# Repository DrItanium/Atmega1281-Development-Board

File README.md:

This is a simple development board for the QFP version of the ATMEGA1281. The
layout of the connector is an extended superset of the digital header found on
the Arduino Mega + an internal MajorCore development board I have also
created. 

The rest of the pins are laid out to make it trivial to design plugin boards
for my ecore and SxChipset projects.

The board is designed for the AISLER PCB manufacturing service.

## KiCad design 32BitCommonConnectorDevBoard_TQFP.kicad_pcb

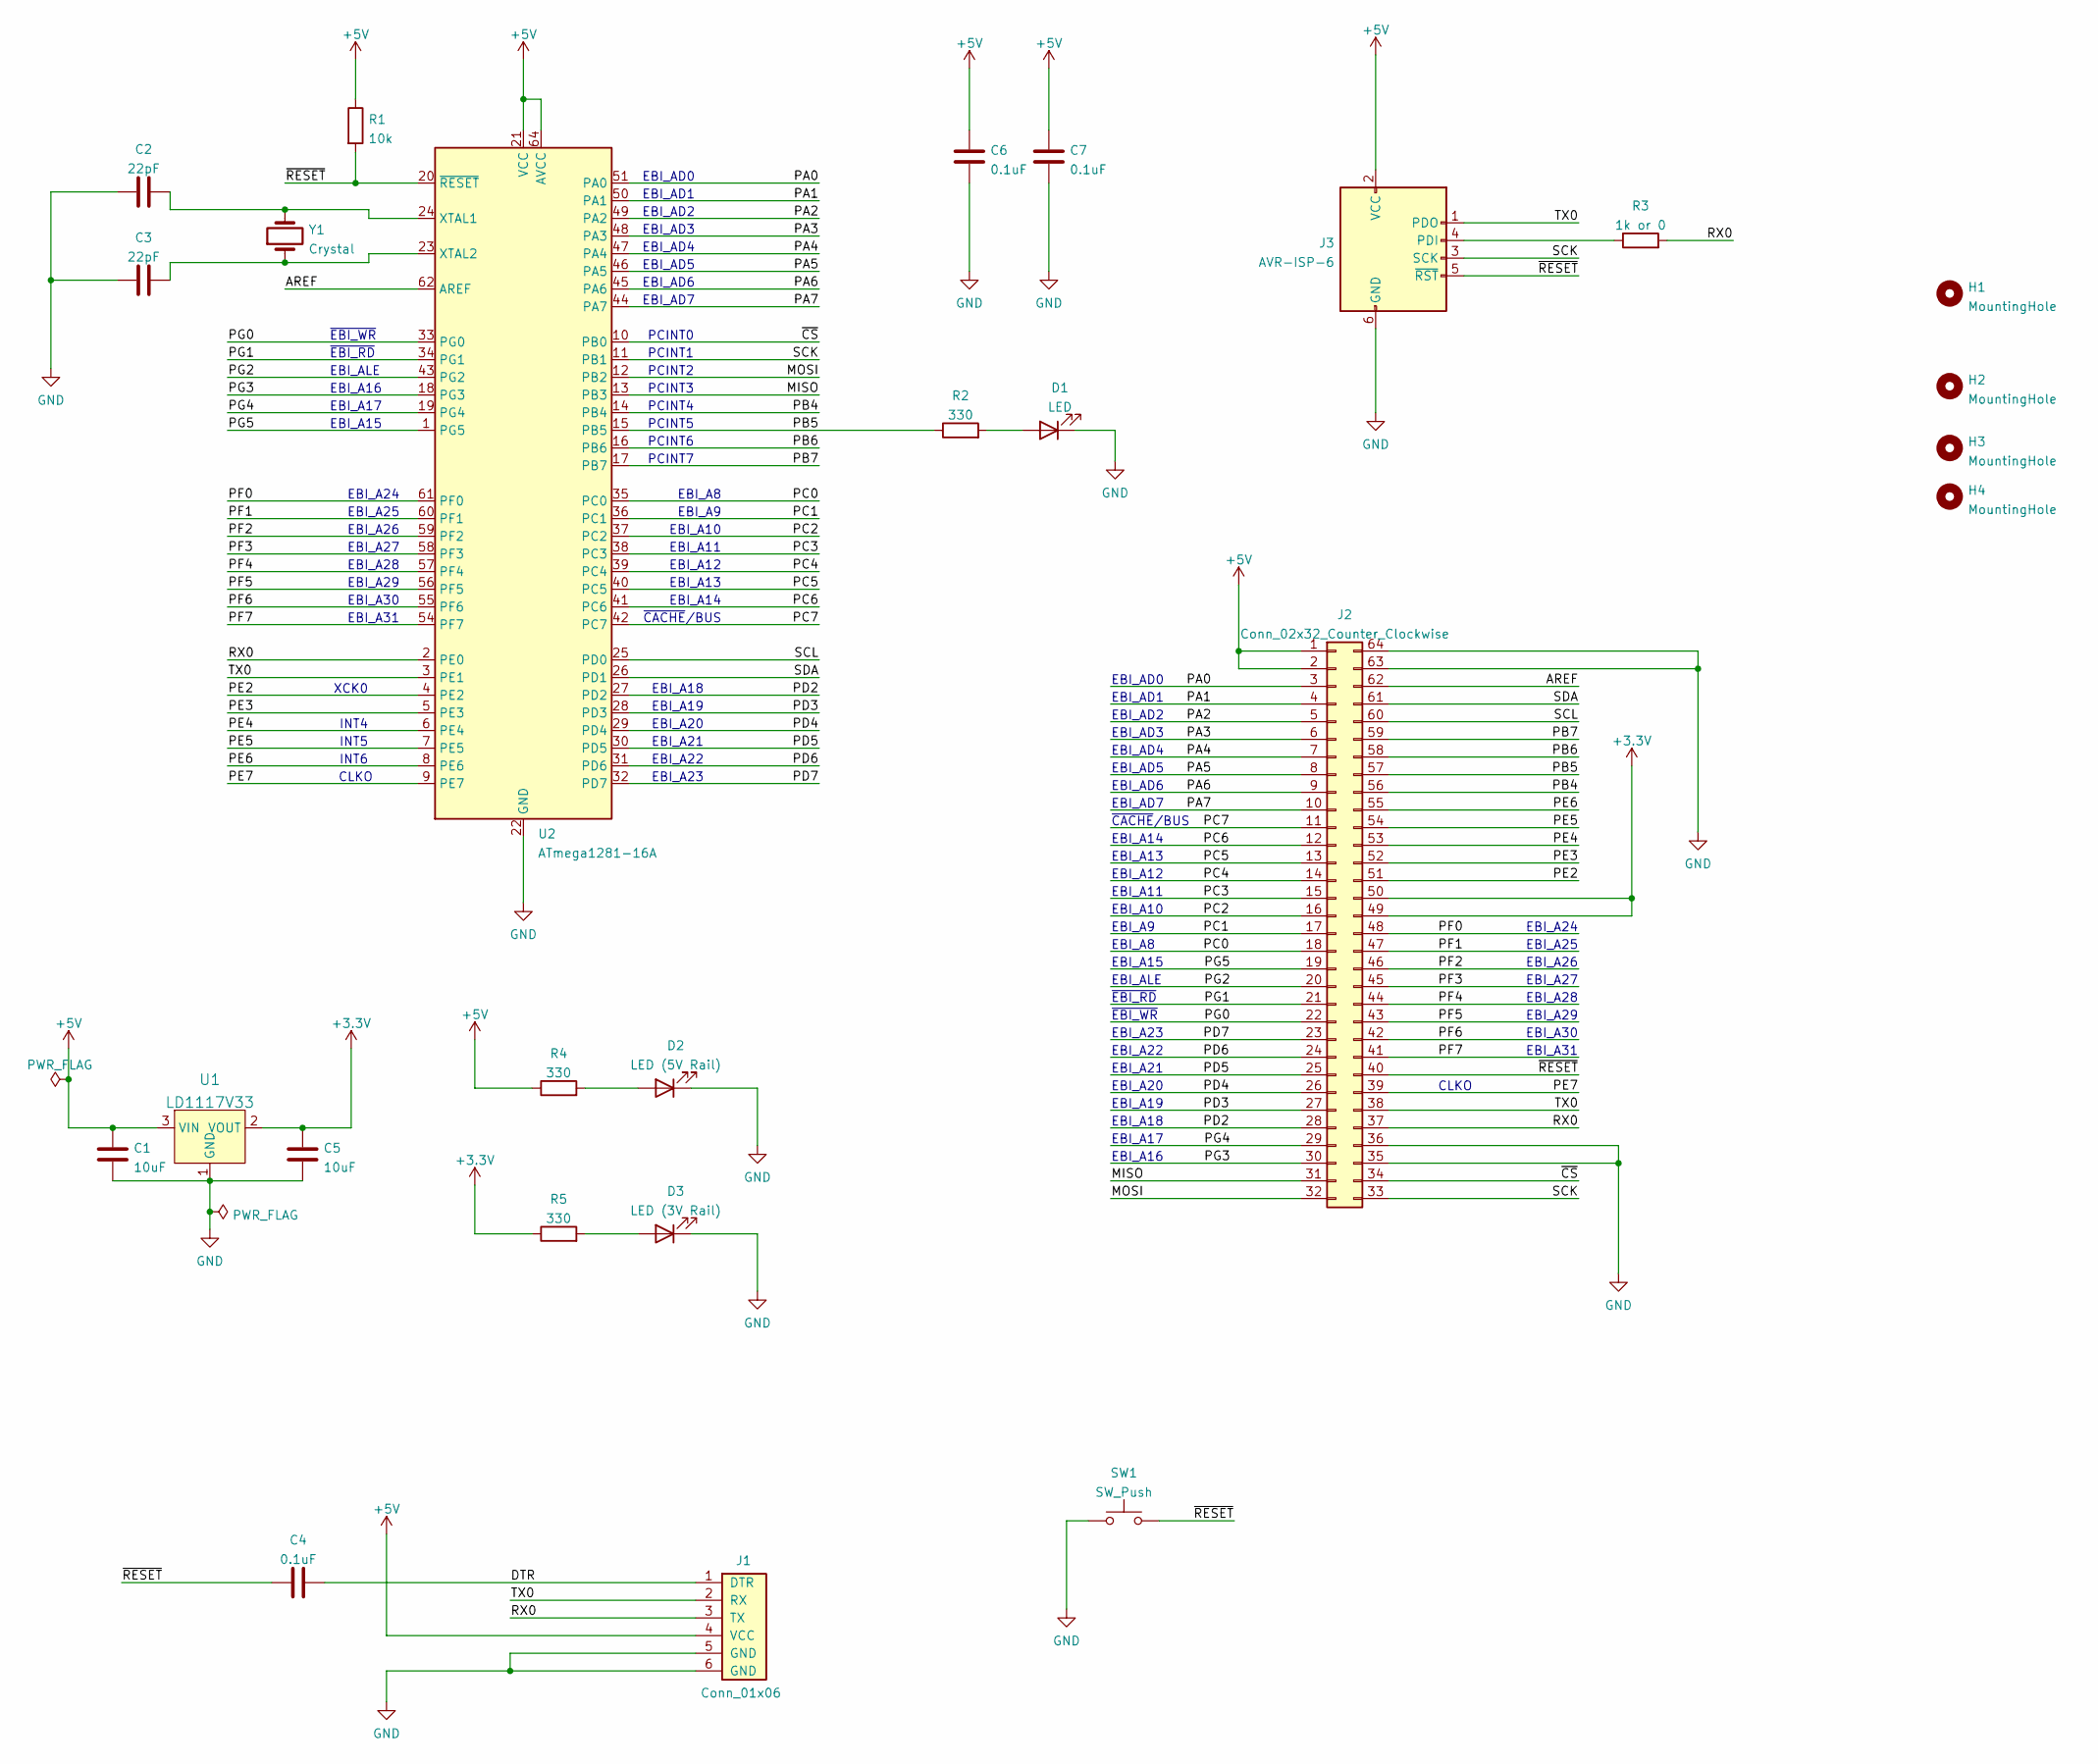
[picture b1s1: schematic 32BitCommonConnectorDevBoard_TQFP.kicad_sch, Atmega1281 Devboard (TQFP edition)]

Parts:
C1, C5: 10uF; C_0805_2012Metric_Pad1.18x1.45mm_HandSolder
C2, C3: 22pF; C_0805_2012Metric_Pad1.18x1.45mm_HandSolder
C4, C6, C7: 0.1uF; C_0805_2012Metric_Pad1.18x1.45mm_HandSolder
D1: LED; LED_D5.0mm
D2: LED (5V Rail); LED_D5.0mm
D3: LED (3V Rail); LED_D5.0mm
H1, H2, H3, H4: MountingHole; MountingHole_3.2mm_M3
J1: Conn_01x06; PinHeader_1x06_P2.54mm_Vertical
J2: Conn_02x32_Counter_Clockwise; PinSocket_2x32_P2.54mm_Vertical
J3: AVR-ISP-6; PinHeader_2x03_P2.54mm_Vertical
R1: 10k; R_0805_2012Metric_Pad1.20x1.40mm_HandSolder
R2, R4, R5: 330; R_0805_2012Metric_Pad1.20x1.40mm_HandSolder
R3: 1k or 0; R_0805_2012Metric_Pad1.20x1.40mm_HandSolder
SW1: SW_Push; SW_PUSH_6mm
U1: LD1117V33; TO-220-3; MPN LD1117V33; Digi-Key_PN 497-1491-5-ND
U2: ATmega1281-16A; TQFP-64_14x14mm_P0.8mm
Y1: Crystal; Crystal_HC49-U_Vertical

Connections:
+3V3: C5.1, J2.49, J2.50, R5.1, U1.2 (VOUT)
+5V: C1.1, C6.1, C7.1, J1.4 (VCC), J2.1, J2.2, J3.2 (VCC), R1.1, R4.1, U1.3 (VIN), U2.21 (VCC), U2.52 (VCC), U2.64 (AVCC)
/AREF: J2.62, U2.62 (AREF)
/DTR: C4.1, J1.1 (DTR)
/MISO: J2.31, U2.13 (PB3)
/MOSI: J2.32, U2.12 (PB2)
/PA0: J2.3, U2.51 (PA0)
/PA1: J2.4, U2.50 (PA1)
/PA2: J2.5, U2.49 (PA2)
/PA3: J2.6, U2.48 (PA3)
/PA4: J2.7, U2.47 (PA4)
/PA5: J2.8, U2.46 (PA5)
/PA6: J2.9, U2.45 (PA6)
/PA7: J2.10, U2.44 (PA7)
/PB4: J2.56, U2.14 (PB4)
/PB5: J2.57, R2.1, U2.15 (PB5)
/PB6: J2.58, U2.16 (PB6)
/PB7: J2.59, U2.17 (PB7)
/PC0: J2.18, U2.35 (PC0)
/PC1: J2.17, U2.36 (PC1)
/PC2: J2.16, U2.37 (PC2)
/PC3: J2.15, U2.38 (PC3)
/PC4: J2.14, U2.39 (PC4)
/PC5: J2.13, U2.40 (PC5)
/PC6: J2.12, U2.41 (PC6)
/PC7: J2.11, U2.42 (PC7)
/PD2: J2.28, U2.27 (PD2)
/PD3: J2.27, U2.28 (PD3)
/PD4: J2.26, U2.29 (PD4)
/PD5: J2.25, U2.30 (PD5)
/PD6: J2.24, U2.31 (PD6)
/PD7: J2.23, U2.32 (PD7)
/PE2: J2.51, U2.4 (PE2)
/PE3: J2.52, U2.5 (PE3)
/PE4: J2.53, U2.6 (PE4)
/PE5: J2.54, U2.7 (PE5)
/PE6: J2.55, U2.8 (PE6)
/PE7: J2.39, U2.9 (PE7)
/PF0: J2.48, U2.61 (PF0)
/PF1: J2.47, U2.60 (PF1)
/PF2: J2.46, U2.59 (PF2)
/PF3: J2.45, U2.58 (PF3)
/PF4: J2.44, U2.57 (PF4)
/PF5: J2.43, U2.56 (PF5)
/PF6: J2.42, U2.55 (PF6)
/PF7: J2.41, U2.54 (PF7)
/PG0: J2.22, U2.33 (PG0)
/PG1: J2.21, U2.34 (PG1)
/PG2: J2.20, U2.43 (PG2)
/PG3: J2.30, U2.18 (PG3)
/PG4: J2.29, U2.19 (PG4)
/PG5: J2.19, U2.1 (PG5)
/RX0: J1.3 (TX), J2.37, R3.2, U2.2 (PE0)
/SCK: J2.33, J3.3 (SCK), U2.11 (PB1)
/SCL: J2.60, U2.25 (PD0)
/SDA: J2.61, U2.26 (PD1)
/TX0: J1.2 (RX), J2.38, J3.1 (PDO), U2.3 (PE1)
/~CS: J2.34, U2.10 (PB0)
/~RESET: C4.2, J2.40, J3.5 (~RST), R1.2, SW1.2, U2.20 (~RESET)
GND: C1.2, C2.1, C3.1, C5.2, C6.2, C7.2, D1.1 (K), D2.1 (K), D3.1 (K), J1.5 (GND), J1.6 (GND), J2.35, J2.36, J2.63, J2.64, J3.6 (GND), SW1.1, U1.1 (GND), U2.22 (GND), U2.53 (GND), U2.63 (GND)
unnamed: C2.2, U2.24 (XTAL1), Y1.2
unnamed: C3.2, U2.23 (XTAL2), Y1.1
unnamed: D1.2 (A), R2.2
unnamed: D2.2 (A), R4.2
unnamed: D3.2 (A), R5.2
unnamed: J3.4 (PDI), R3.1

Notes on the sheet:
EBI_A27
INT4
EBI_A29
INT5
CLKO
EBI_A21
EBI_A17
EBI_A31
PCINT3
EBI_A8
PCINT2
EBI_A28
EBI_A12
EBI_AD5
EBI_A24
EBI_A16
PCINT0
EBI_AD0
EBI_A14
EBI_A19
EBI_AD7
EBI_AD3
EBI_A13
EBI_A22
EBI_AD4
PCINT6
EBI_A23
EBI_AD1
~{EBI_RD}
EBI_AD6
~{CACHE}/BUS
PCINT1
EBI_A26
EBI_ALE
EBI_A25
PCINT5
XCK0
PCINT7
~{EBI_WR}
INT6

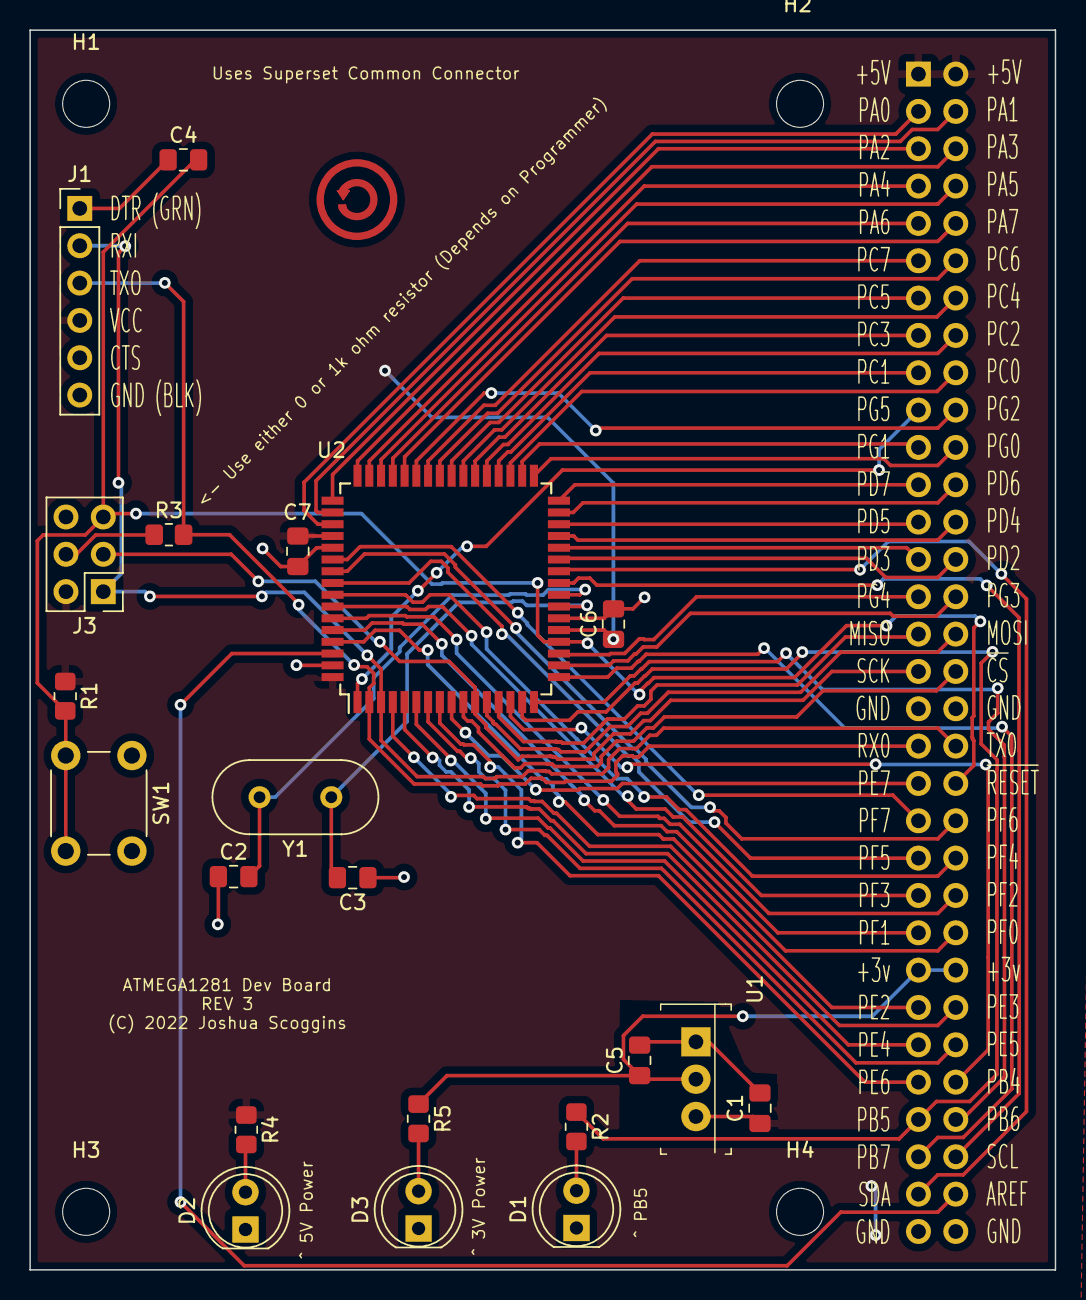
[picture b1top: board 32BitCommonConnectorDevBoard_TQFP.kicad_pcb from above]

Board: 2 copper layers, 69.8 x 84.3 mm, 26 parts (1 on the bottom side), 66 nets.

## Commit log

2022-02-15 Added a readme
2022-02-15 Rename the schematic pins to reflect port ids
    The EBI layout is implied by the design
2022-02-15 Clean up layouts and shrink board slightly
2022-02-15 Added a license
2022-02-15 Move PE7 to position 39 on the connector
    PG5 is now in place of PB7
    Rearrange left over port B so it is:
    59 -> PB7
    58 -> PB6
    57 -> PB5
    56 -> PB4
2022-02-15 Update revision number and put share alike logo back in

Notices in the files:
32BitCommonConnectorDevBoard_TQFP.kicad_pcb:
(C) 2022 Joshua Scoggins
